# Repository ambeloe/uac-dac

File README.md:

# uac-dac
usb uac1 dac using the pcm2903 and a max13330geev amplifier; incorrect pin numbering on 3v3 regulator and missing d+ pullup
wrong footprint for usb receptacle shield

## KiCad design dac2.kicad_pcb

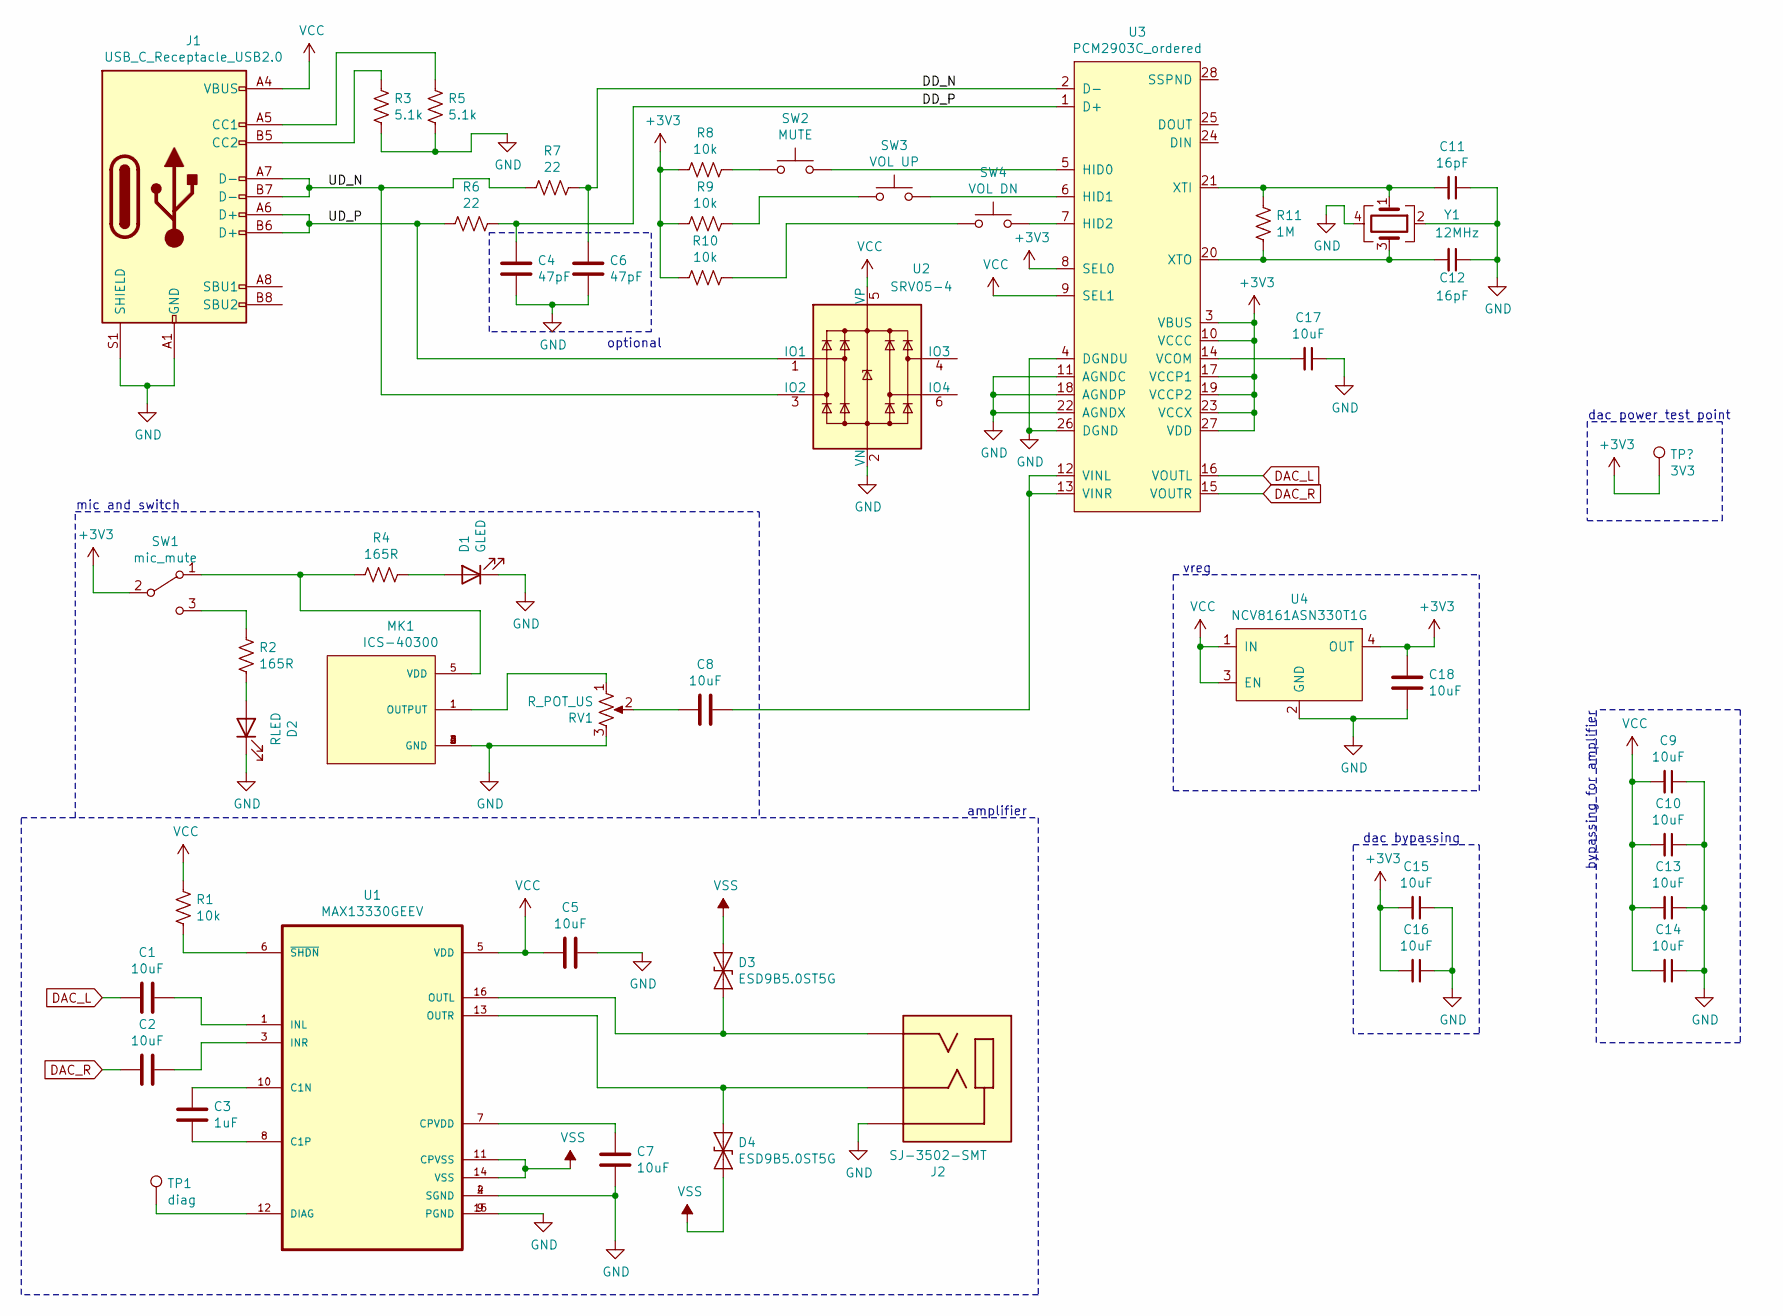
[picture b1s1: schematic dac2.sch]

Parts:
C1, C2, C5, C7, C8, C9, C10, C13, C14, C15, C16, C17, C18: 10uF; C_0603_1608Metric
C3: 1uF; C_0402_1005Metric_Pad0.74x0.62mm_HandSolder
C4, C6: 47pF; C_0402_1005Metric_Pad0.74x0.62mm_HandSolder
C11, C12: 16pF; C_0402_1005Metric_Pad0.74x0.62mm_HandSolder
D1: GLED; LED_0805_2012Metric_Pad1.15x1.40mm_HandSolder
D2: RLED; LED_0805_2012Metric_Pad1.15x1.40mm_HandSolder
D3, D4: ESD9B5.0ST5G; D_SOD-923
J1: USB_C_Receptacle_USB2.0; GCT_USB4085
J2: SJ-3502-SMT; CUI_SJ-3502-SMT
MK1: ICS-40300; MIC_ICS-40300
R1, R8, R9, R10: 10k; C_0603_1608Metric
R2, R4: 165R; C_0603_1608Metric
R3, R5: 5.1k; C_0603_1608Metric
R6, R7: 22; C_0402_1005Metric_Pad0.74x0.62mm_HandSolder
R11: 1M; C_0603_1608Metric
RV1: R_POT_US; ST-4EA
SW1: mic_mute; AYZ0102AGRLC
SW2: MUTE; EVQ-P7K01P
SW3: VOL UP; EVQ-P7K01P
SW4: VOL DN; EVQ-P7K01P
TP1: diag; TestPoint_Pad_1.5x1.5mm
U1: MAX13330GEEV; SOP63P602X175-16N
U2: SRV05-4; SOT-23-6
U3: PCM2903C_ordered; SSOP-28_5.3x10.2mm_P0.65mm
U4: NCV8161ASN330T1G; TSOT-23-5
Y1: 12MHz; Crystal_SMD_3225-4Pin_3.2x2.5mm

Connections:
+3V3: C15.2, C16.2, C18.1, R8.2, R9.2, R10.2, SW1.2 (B), U3.3 (VBUS), U3.8 (SEL0), U3.10 (VCCC), U3.17 (VCCP1), U3.19 (VCCP2), U3.23 (VCCX), U3.27 (VDD), U4.4 (OUT)
/DD_N: C6.1, R7.1, U3.2 (D-)
/DD_P: C4.1, R6.1, U3.1 (D+)
/UD_N: J1.A7 (D-), J1.B7 (D-), R7.2, U2.3 (IO2)
/UD_P: J1.A6 (D+), J1.B6 (D+), R6.2, U2.1 (IO1)
DAC_L: C1.2, U3.16 (VOUTL)
DAC_R: C2.2, U3.15 (VOUTR)
unnamed: C1.1, U1.1 (INL)
unnamed: C2.1, U1.3 (INR)
unnamed: C3.1, U1.10 (C1N)
unnamed: C3.2, U1.8 (C1P)
unnamed: C7.2, U1.7 (CPVDD)
unnamed: C8.1, U3.12 (VINL), U3.13 (VINR)
unnamed: C8.2, RV1.2
unnamed: C11.2, R11.1, U3.21 (XTI), Y1.1
unnamed: C12.2, R11.2, U3.20 (XTO), Y1.3
unnamed: C17.2, U3.14 (VCOM)
unnamed: D1.2 (A), R4.1
unnamed: D2.2 (A), R2.2
unnamed: D3.2 (A2), J2.2, U1.16 (OUTL)
unnamed: D4.1 (A1), J2.3, U1.13 (OUTR)
unnamed: J1.A5 (CC1), R5.1
unnamed: J1.B5 (CC2), R3.1
unnamed: MK1.1 (OUTPUT), RV1.1
unnamed: MK1.5 (VDD), R4.2, SW1.1 (A)
unnamed: R1.2, U1.6 (~SHDN)
unnamed: R2.1, SW1.3 (C)
unnamed: R8.1, SW2.1
unnamed: R9.1, SW3.1
unnamed: R10.1, SW4.1
unnamed: SW2.2, U3.5 (HID0)
unnamed: SW3.2, U3.6 (HID1)
unnamed: SW4.2, U3.7 (HID2)
unnamed: TP1.1, U1.12 (DIAG)
VCC: C5.2, C9.2, C10.2, C13.2, C14.2, J1.A4 (VBUS), J1.A9 (VBUS), J1.B4 (VBUS), J1.B9 (VBUS), R1.1, U1.5 (VDD), U2.5 (VP), U3.9 (SEL1), U4.1 (IN), U4.3 (EN)
VSS: D3.1 (A1), D4.2 (A2), U1.11 (CPVSS), U1.14 (VSS)

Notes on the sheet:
mic and switch
amplifier
vreg
optional
bypassing for amplifier
dac bypassing
dac power test point

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
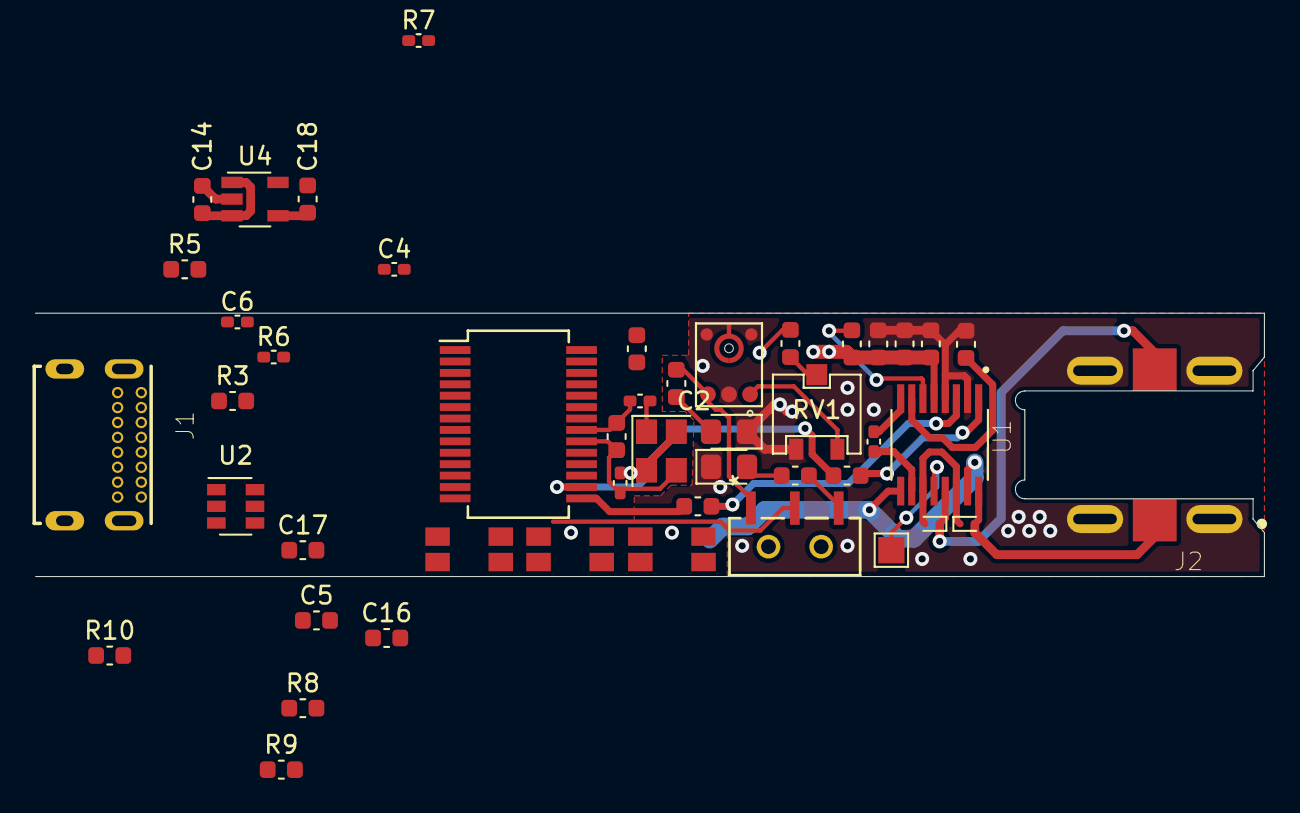
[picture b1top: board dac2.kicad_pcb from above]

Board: 2 copper layers, 70.0 x 15.0 mm, 47 parts (0 on the bottom side), 38 nets.
